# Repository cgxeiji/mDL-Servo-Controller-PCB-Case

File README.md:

# Servo Controller PCB w/Case

This PCB integrates a Teensy 3.6 with Adafruit's Servo Motor Controller, and a DC power input.
Includes a 3D printable case.

## How to use?
### What you need:
 - Solder Iron
 - Solder Wire
 - [Teensy 3.6](https://www.sparkfun.com/products/14057)
 - [Adafruit's Servo Driver](https://www.adafruit.com/product/815)
 - DC Power Plug
 - Female / Male Pin Headers
> This build assumes you know how to make a PCB.

### PCB
1. Make the PCB with your prefered method.
1. Solder `female pin headers` to the board if you want to be able to reuse the **Teensy** and **Adafruit's Servo Motor** modules. (The 3D Print Case was designed considering female pin headers height)
1. Cut the **USB Power** connection from the **Teensy**.
1. Solder `male pin headers` to the **modules** and a `DC power plug` to the **board**.
1. `Attention!!!` Make sure to assemble the modules in the correct orientation.

### 3D Print Case
1. You can directly print the `.stl` files ([case](3D%20Case/Case.stl "../3D Case/Case.stl") / [lid](3D%20Case/Lid.stl "../3D Case/Lid.stl")) provided or open the Fusion 360 [file](3D%20Case/Fusion%20360%20Files/Case.f3d "../3D Case/Fusion 360 Files/Case.f3d") and export the file to your preferred 3D Print software.
1. Fit the **PCB** inside the **case**.
1. Close the **case** with the **lid**.
1. Done!

> If you do not use female pin headers, you will need to adjust the height of the case.

## About this project
This project is part of the **Digital Fabrication** course at **KAIST**, South Korea.

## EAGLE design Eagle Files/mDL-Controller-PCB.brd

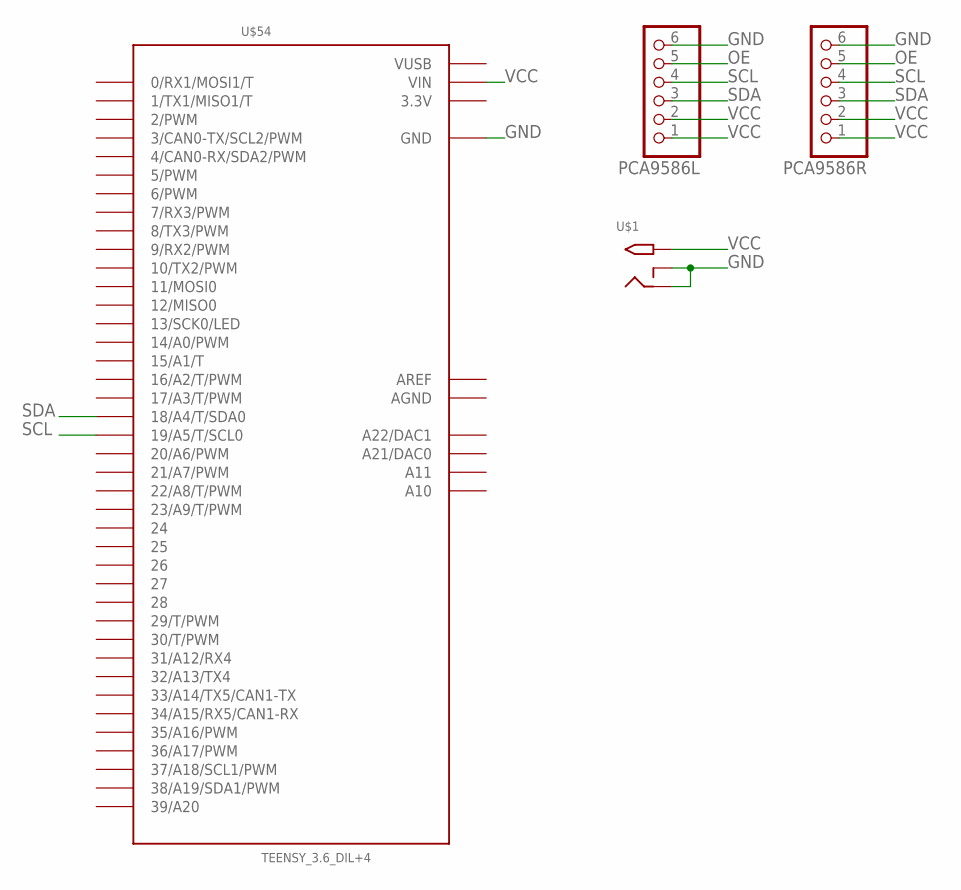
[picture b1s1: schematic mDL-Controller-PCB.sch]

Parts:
PCA9586L, PCA9586R: PINHD-1X6B; 1X06-BIG
U$1: 2.1MMJACKTHM; PJ-102A
U$54: TEENSY_3.6_DIL+4

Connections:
3.3V: U$54.3.3V, U$54.3.3V3 (3.3V)
AGND: U$54.AGND
AREF: U$54.AREF
GND: PCA9586L.6, PCA9586R.6, U$1.RING, U$1.RING_SW, U$54.GND, U$54.GND1 (GND)
OE: PCA9586L.5, PCA9586R.5
SCL: PCA9586L.4, PCA9586R.4, U$54.19/A5 (19/A5/T/SCL0)
SDA: PCA9586L.3, PCA9586R.3, U$54.18/A4 (18/A4/T/SDA0)
VCC: PCA9586L.1, PCA9586L.2, PCA9586R.1, PCA9586R.2, U$1.TIP, U$54.VIN
VUSB: U$54.VUSB

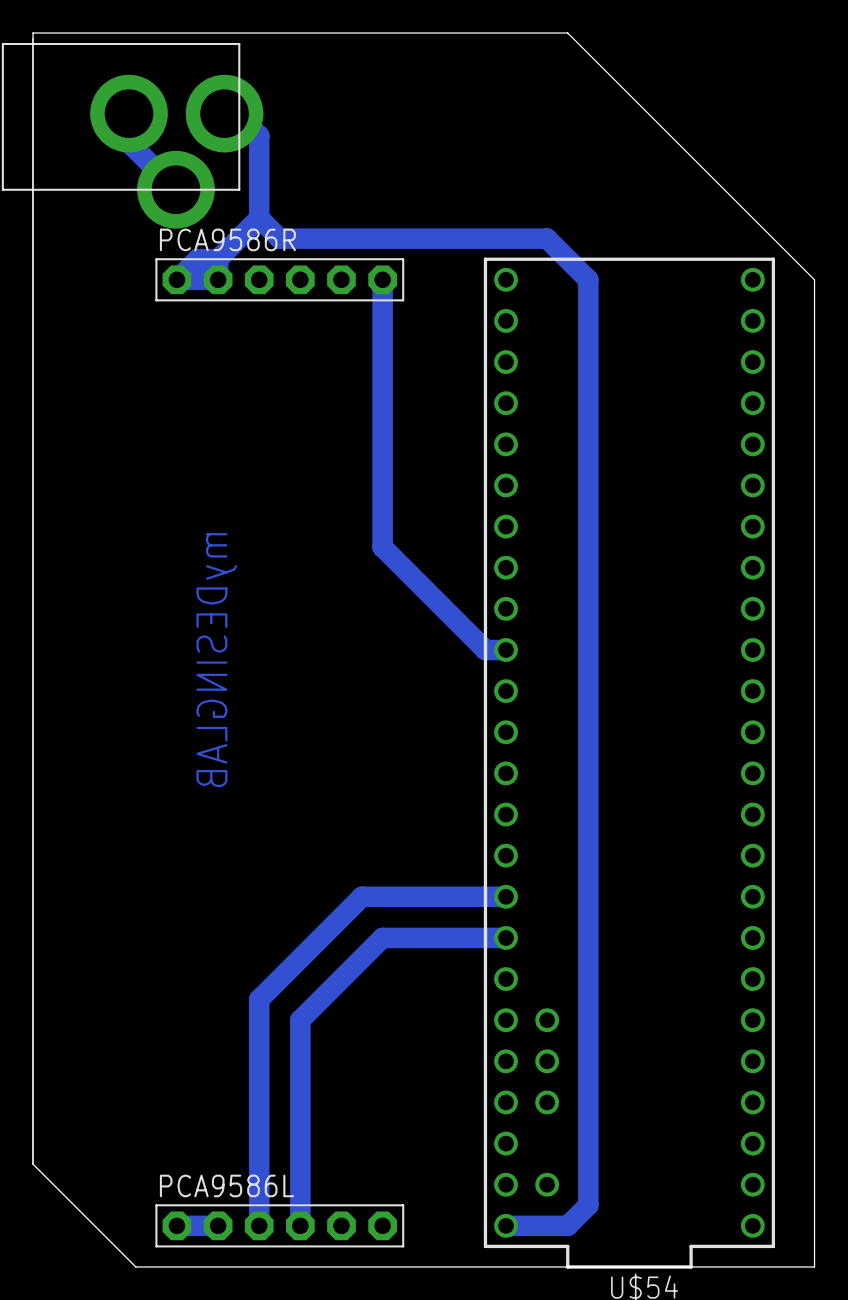
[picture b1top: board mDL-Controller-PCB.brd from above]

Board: 2 copper layers, 48.3 x 76.2 mm, 4 parts (0 on the bottom side), 6 nets.

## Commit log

2017-09-25 Renamed the file
2017-09-25 Added reference images
2017-09-25 Added instructions
2017-09-25 Resized the images
2017-09-25 Added information about the project
2017-09-25 Changed the position of the first sentence
2017-09-25 Added materials list
2017-09-25 Added extra information about pin headers
2017-09-26 Fixed a typo
